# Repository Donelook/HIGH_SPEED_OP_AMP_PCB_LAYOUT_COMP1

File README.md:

[HIGH_SPEED_OP_AMP_PCB_LAYOUT_COMP1_schen.pdf](https://github.com/user-attachments/files/28200884/HIGH_SPEED_OP_AMP_PCB_LAYOUT_COMP1_schen.pdf)

[HIGH_SPEED_OP_AMP_PCB_LAYOUT_COMP1__Assembly.pdf](https://github.com/user-attachments/files/28200890/HIGH_SPEED_OP_AMP_PCB_LAYOUT_COMP1__Assembly.pdf)

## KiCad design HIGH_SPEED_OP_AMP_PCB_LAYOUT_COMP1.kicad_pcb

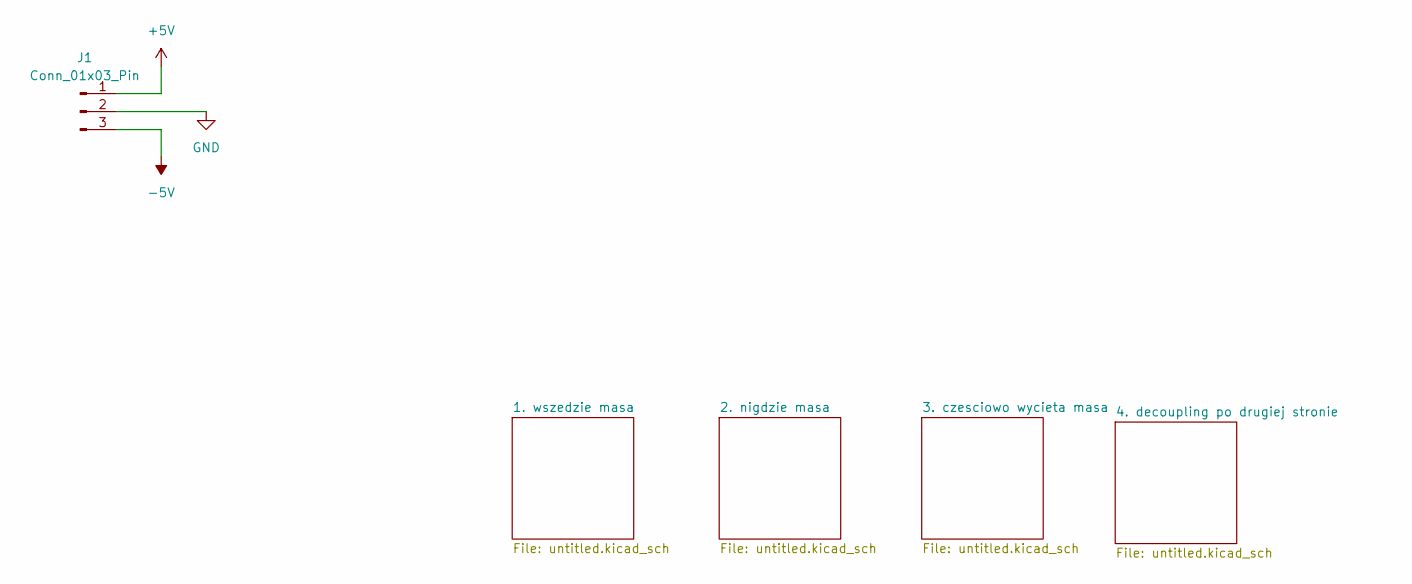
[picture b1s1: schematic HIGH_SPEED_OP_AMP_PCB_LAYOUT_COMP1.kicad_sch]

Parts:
J1: Conn_01x03_Pin; PinHeader_1x03_P2.54mm_Vertical

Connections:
+5V: J1.1; also elsewhere on the board
-5V: J1.3; also elsewhere on the board
GND: J1.2; also elsewhere on the board

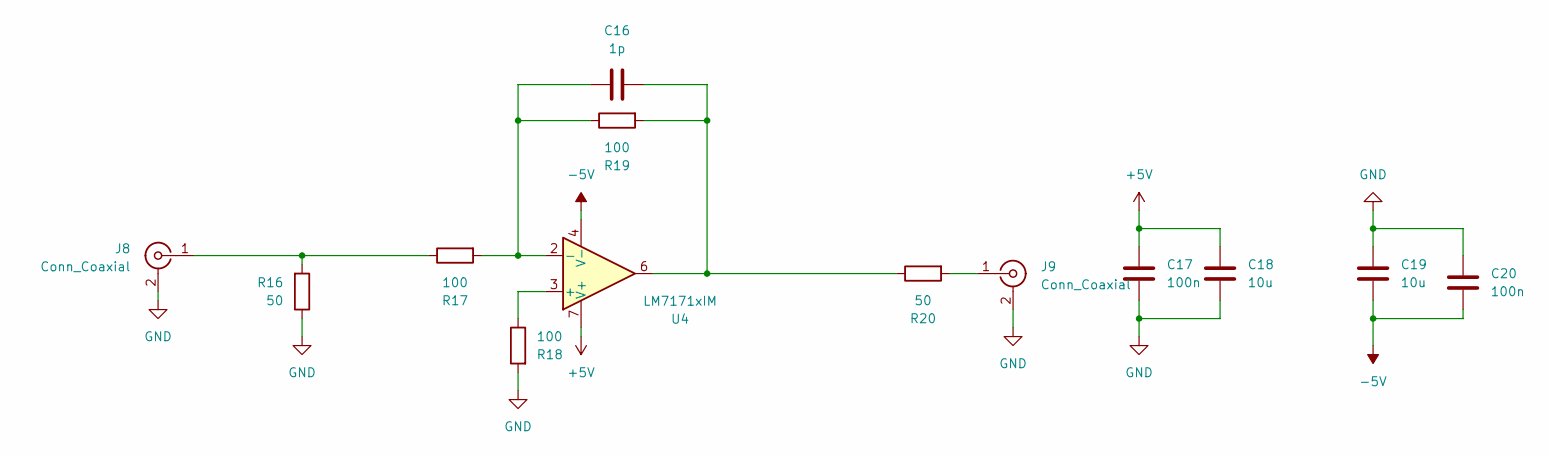
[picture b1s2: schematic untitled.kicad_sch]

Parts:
C16: 1p; C_0603_1608Metric_Pad1.08x0.95mm_HandSolder
C17, C20: 100n; C_0603_1608Metric_Pad1.08x0.95mm_HandSolder
C18, C19: 10u; C_1206_3216Metric_Pad1.33x1.80mm_HandSolder
J8, J9: Conn_Coaxial; SMA_Amphenol_901-143_Horizontal
R16, R20: 50; R_0603_1608Metric_Pad0.98x0.95mm_HandSolder
R17, R18, R19: 100; R_0603_1608Metric_Pad0.98x0.95mm_HandSolder
U4: LM7171xIM; SOIC-8_3.9x4.9mm_P1.27mm

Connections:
+5V: C17.1, C18.1, U4.7 (V+); also elsewhere on the board
-5V: C19.2, C20.2, U4.4 (V-); also elsewhere on the board
GND: C17.2, C18.2, C19.1, C20.1, J8.2 (Ext), J9.2 (Ext), R16.1, R18.2; also elsewhere on the board
unnamed: C16.2, R19.2, R20.1, U4.6
unnamed: J8.1 (In), R16.2, R17.1
unnamed: J9.1 (In), R20.2
unnamed: R18.1, U4.3 (+)
unnamed: C16.1, R17.2, R19.1, U4.2 (-)

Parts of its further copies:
C1, C6, C11: 1p; C_0603_1608Metric_Pad1.08x0.95mm_HandSolder
C2, C5, C7, C10, C12, C15: 100n; C_0603_1608Metric_Pad1.08x0.95mm_HandSolder
C3, C4, C8, C9, C13, C14: 10u; C_1206_3216Metric_Pad1.33x1.80mm_HandSolder
J2, J3, J4, J5, J6, J7: Conn_Coaxial; SMA_Amphenol_901-143_Horizontal
R1, R5, R6, R10, R11, R15: 50; R_0603_1608Metric_Pad0.98x0.95mm_HandSolder
R2, R3, R4, R7, R8, R9, R12, R13, R14: 100; R_0603_1608Metric_Pad0.98x0.95mm_HandSolder
U1, U2, U3: LM7171xIM; SOIC-8_3.9x4.9mm_P1.27mm

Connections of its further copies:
+5V: C2.1, C3.1, C7.1, C8.1, C12.1, C13.1, U1.7 (V+), U2.7 (V+), U3.7 (V+); also elsewhere on the board
-5V: C4.2, C5.2, C9.2, C10.2, C14.2, C15.2, U1.4 (V-), U2.4 (V-), U3.4 (V-); also elsewhere on the board
GND: C2.2, C3.2, C4.1, C5.1, C7.2, C8.2, C9.1, C10.1, C12.2, C13.2, C14.1, C15.1, J2.2 (Ext), J3.2 (Ext), J4.2 (Ext), J5.2 (Ext), J6.2 (Ext), J7.2 (Ext), R1.1, R3.2, R6.1, R8.2, R11.1, R13.2; also elsewhere on the board
unnamed: C1.2, R4.2, R5.1, U1.6
unnamed: C6.2, R9.2, R10.1, U2.6
unnamed: C11.2, R14.2, R15.1, U3.6
unnamed: J2.1 (In), R1.2, R2.1
unnamed: J3.1 (In), R5.2
unnamed: J4.1 (In), R6.2, R7.1
unnamed: J5.1 (In), R10.2
unnamed: J6.1 (In), R11.2, R12.1
unnamed: J7.1 (In), R15.2
unnamed: R3.1, U1.3 (+)
unnamed: C1.1, R2.2, R4.1, U1.2 (-)
unnamed: R8.1, U2.3 (+)
unnamed: C6.1, R7.2, R9.1, U2.2 (-)
unnamed: R13.1, U3.3 (+)
unnamed: C11.1, R12.2, R14.1, U3.2 (-)

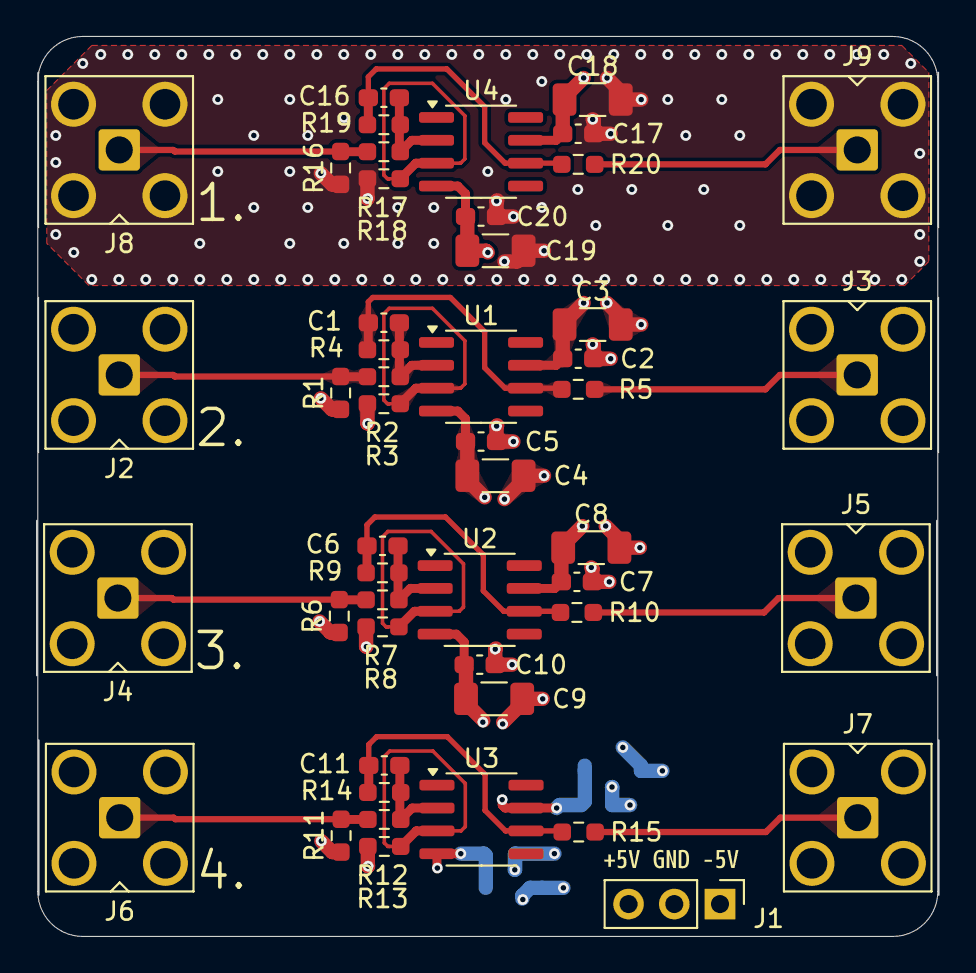
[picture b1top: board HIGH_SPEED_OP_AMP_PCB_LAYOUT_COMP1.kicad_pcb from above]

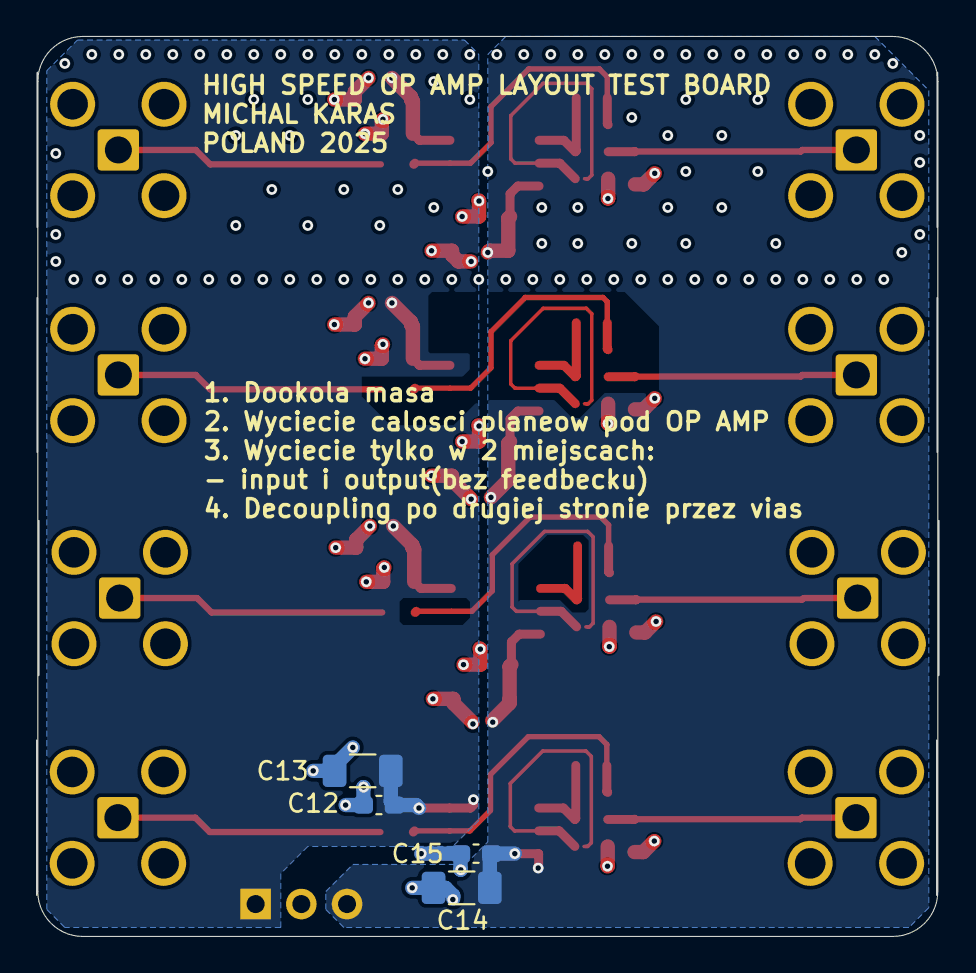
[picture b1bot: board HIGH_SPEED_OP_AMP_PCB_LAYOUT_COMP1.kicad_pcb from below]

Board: 4 copper layers, 50.1 x 50.0 mm, 54 parts (4 on the bottom side), 23 nets.

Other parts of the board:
kibuzzard-6938C394: G***; kibuzzard-6938C394

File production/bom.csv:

Designator,Footprint,Quantity,Value,LCSC Part #
"C1, C11, C16, C6",0603,4,1p,
"C10, C12, C15, C17, C2, C20, C5, C7",0603,8,100n,
"C13, C14, C18, C19, C3, C4, C8, C9",1206,8,10u,
J1,PinHeader_1x03_P2.54mm_Vertical,1,Conn_01x03_Pin,
"J2, J3, J4, J5, J6, J7, J8, J9",SMA_Amphenol_901-143_Horizontal,8,Conn_Coaxial,
"R1, R10, R11, R15, R16, R20, R5, R6",0603,8,50,
"R12, R13, R14, R17, R18, R19, R2, R3, R4, R7, R8, R9",0603,12,100,
"U1, U2, U3, U4",SOIC-8_3.9x4.9mm_P1.27mm,4,LM7171xIM,

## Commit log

2026-05-24 testy
